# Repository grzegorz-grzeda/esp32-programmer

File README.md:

# ESP32 Programmer

This is a KiCAD 7 PCB project for the ESP32 Programmer.

Some photos:

## Copyright
CC-BY 4.0
Created by G2Labs Grzegorz Grzęda

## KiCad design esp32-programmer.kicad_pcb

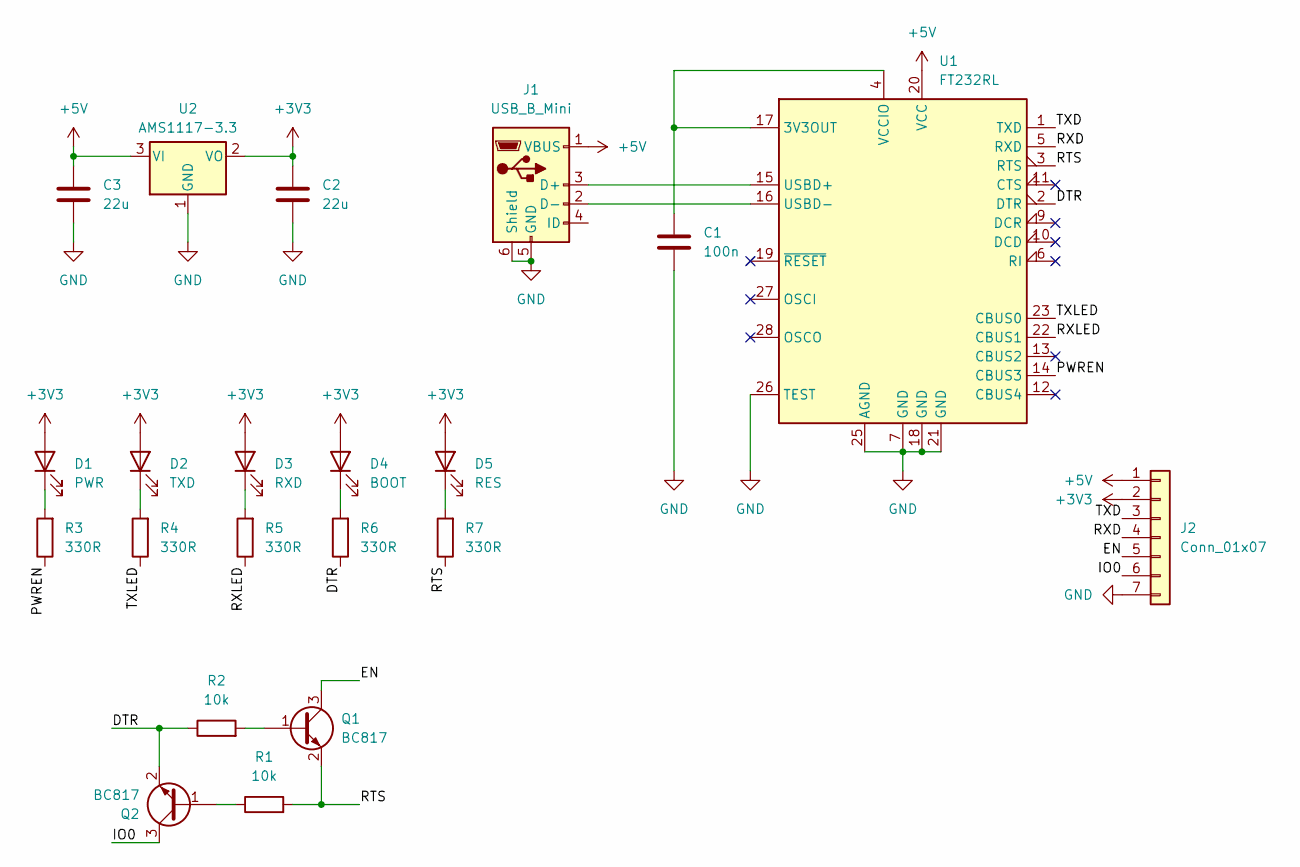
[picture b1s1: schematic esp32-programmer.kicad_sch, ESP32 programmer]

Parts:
C1: 100n; C_1206_3216Metric_Pad1.33x1.80mm_HandSolder
C2, C3: 22u; C_1206_3216Metric_Pad1.33x1.80mm_HandSolder
D1: PWR; LED_1206_3216Metric
D2: TXD; LED_1206_3216Metric
D3: RXD; LED_1206_3216Metric
D4: BOOT; LED_1206_3216Metric
D5: RES; LED_1206_3216Metric
J1: USB_B_Mini; USB_Mini-B_Lumberg_2486_01_Horizontal
J2: Conn_01x07; PinHeader_1x07_P2.54mm_Vertical
Q1, Q2: BC817; SOT-23
R1, R2: 10k; R_1206_3216Metric_Pad1.30x1.75mm_HandSolder
R3, R4, R5, R6, R7: 330R; R_1206_3216Metric_Pad1.30x1.75mm_HandSolder
U1: FT232RL; SSOP-28_5.3x10.2mm_P0.65mm
U2: AMS1117-3.3; SOT-223-3_TabPin2

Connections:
+3V3: C2.1, D1.2 (A), D2.2 (A), D3.2 (A), D4.2 (A), D5.2 (A), J2.2, U2.2 (VO)
+5V: C3.1, J1.1 (VBUS), J2.1, U1.20 (VCC), U2.3 (VI)
/DTR: Q2.2 (E), R2.1, R6.1, U1.2 (DTR)
/EN: J2.5, Q1.3 (C)
/IO0: J2.6, Q2.3 (C)
/PWREN: R3.1, U1.14 (CBUS3)
/RTS: Q1.2 (E), R1.2, R7.1, U1.3 (RTS)
/RXD: J2.4, U1.5 (RXD)
/RXLED: R5.1, U1.22 (CBUS1)
/TXD: J2.3, U1.1 (TXD)
/TXLED: R4.1, U1.23 (CBUS0)
GND: C1.2, C2.2, C3.2, J1.5 (GND), J1.6 (Shield), J2.7, U1.7 (GND), U1.18 (GND), U1.21 (GND), U1.25 (AGND), U1.26 (TEST), U2.1 (GND)
unnamed: D1.1 (K), R3.2
unnamed: D2.1 (K), R4.2
unnamed: D3.1 (K), R5.2
unnamed: D4.1 (K), R6.2
unnamed: D5.1 (K), R7.2
unnamed: J1.3 (D+), U1.15 (USBD+)
unnamed: J1.2 (D-), U1.16 (USBD-)
unnamed: Q1.1 (B), R2.2
unnamed: Q2.1 (B), R1.1
unnamed: C1.1, U1.4 (VCCIO), U1.17 (3V3OUT)

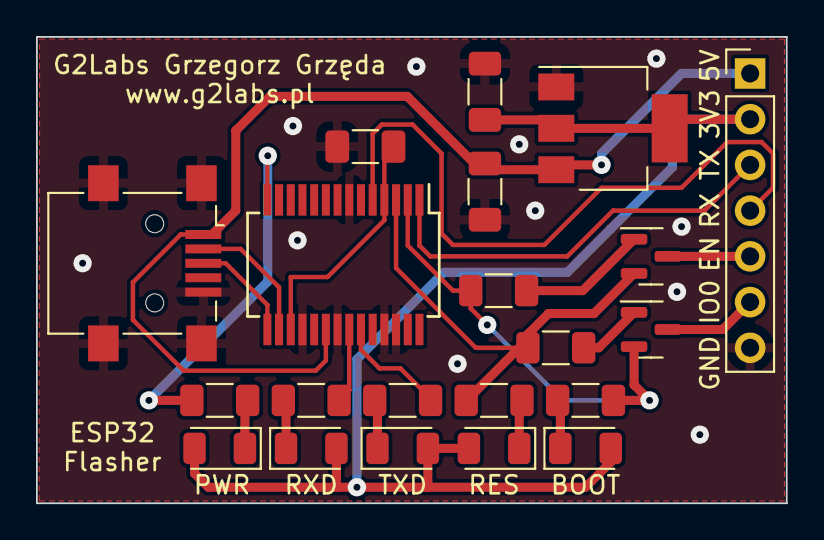
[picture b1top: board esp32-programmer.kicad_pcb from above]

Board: 2 copper layers, 41.7 x 25.9 mm, 21 parts (0 on the bottom side), 22 nets.

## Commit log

2023-09-16 Project initial version
2023-09-16 Added readme
2023-09-20 Create LICENCE
